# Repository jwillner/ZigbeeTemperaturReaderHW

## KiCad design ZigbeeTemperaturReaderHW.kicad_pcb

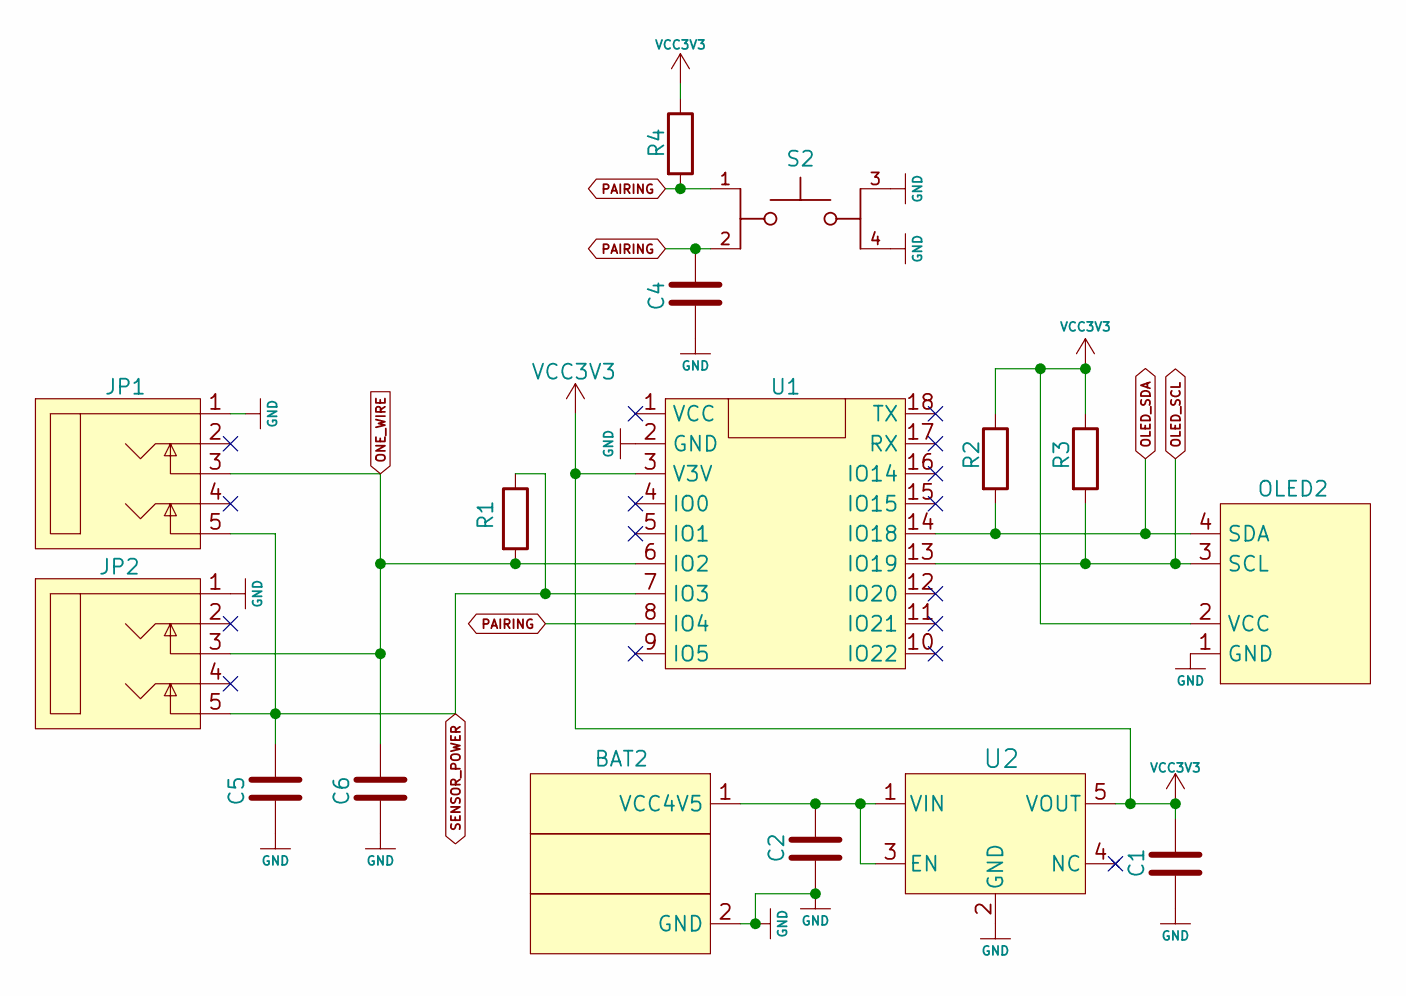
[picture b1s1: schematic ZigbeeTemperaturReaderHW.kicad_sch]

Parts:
BAT2: BatteryHolder_3xAAA
C1, C2, C4, C5: CC1206KRX7R9BB104
C6: CC1206KKX7RDBB102
JP1, JP2: FC68133; JY039-5P
OLED2: OLED-0.96-SSD1306-I2C
R1, R2, R3, R4: RC1206JR-7W1RLC19632287
S2: TL1105BF160Q; SW_TL1105BF160Q; PARTREV A
U1: Waveshare-ESP32-C6-Zero
U2: RT9080-33GJ5; TSOT-23-5_RIT-L

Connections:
GND: BAT2.2 (GND), C1.2, C2.2, C4.2, C5.2, C6.2, JP1.1, JP2.1, OLED2.1 (GND), S2.3, S2.4, U1.2 (GND), U2.2 (GND)
unnamed: BAT2.1 (VCC4V5), C2.1, U2.1 (VIN), U2.3 (EN)
OLED_SCL: OLED2.3 (SCL), R3.2, U1.13 (IO19)
OLED_SDA: OLED2.4 (SDA), R2.2, U1.14 (IO18)
ONE_WIRE: C6.1, JP1.3, JP2.3, R1.2, U1.6 (IO2)
PAIRING: C4.1, R4.2, S2.1, S2.2, U1.8 (IO4)
SENSOR_POWER: C5.1, JP1.5, JP2.5, R1.1, U1.7 (IO3)
VCC3V3: C1.1, OLED2.2 (VCC), R2.1, R3.1, R4.1, U1.3 (V3V), U2.5 (VOUT)

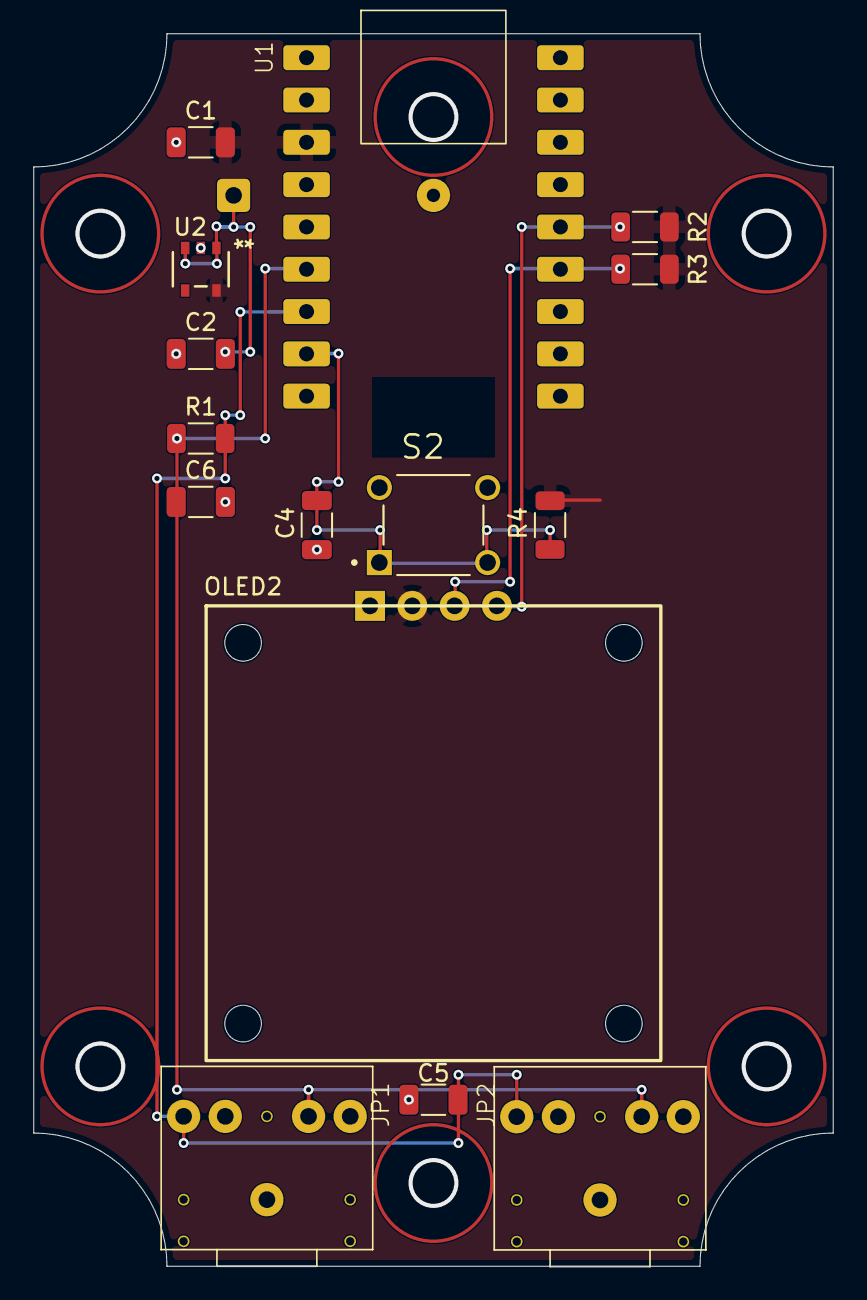
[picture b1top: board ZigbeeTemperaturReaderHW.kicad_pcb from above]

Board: 2 copper layers, 48.0 x 74.0 mm, 16 parts (1 on the bottom side), 8 nets.
